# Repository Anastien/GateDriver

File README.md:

# Gate-Drive
This is a 14 Amp OSHW IGBT gate driver circuit, the layout is done using the KiCad EDA suite, more information cab be found on the the detailed documentation.

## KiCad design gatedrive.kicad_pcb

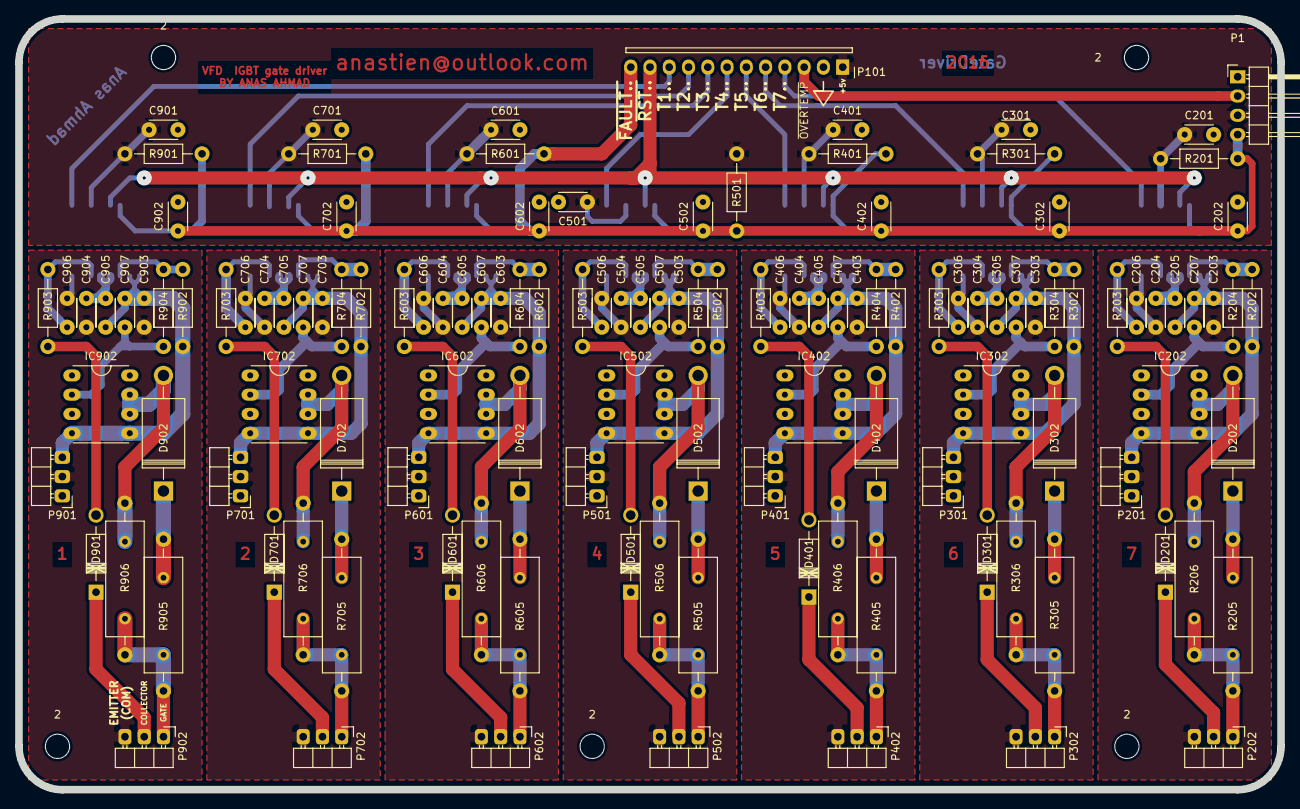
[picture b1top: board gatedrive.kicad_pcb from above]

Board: 2 copper layers, 166.4 x 101.6 mm, 140 parts (0 on the bottom side), 89 nets.

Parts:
2, 2#2, 2#3, 2#4, 2#5: MountingHole_3.2mm_M3
C201, C203, C204, C205, C301, C303, C304, C305, C401, C403, C404, C405, C501, C503, C504, C505, C601, C603, C604, C605, C701, C703, C704, C705, C901, C903, C904, C905: 0.1uF; C_Disc
C202, C302, C402, C502, C602, C702, C902: 330pF; C_Disc
C206, C306, C406, C506, C606, C706, C906: 100pF; C_Disc
C207, C307, C407, C507, C607, C707, C907: 10nF; C_Disc
D201, D301, D401, D501, D601, D701, D901: RGPO2-20; Diode_DO-41_SOD81_Horizontal_RM10
D202, D302, D402, D502, D602, D702, D902: Diode_DO-201AD_Horizontal_RM15
IC201, IC301, IC401, IC501, IC601, IC701, IC901: HCPL-316J; SOIC-16_7.5x10.3mm_Pitch1.27mm
IC202, IC302, IC402, IC502, IC602, IC702, IC902: IXDD614PI; DIP-8_W7.62mm_LongPads
P1: CONN_01X03; Pin_Header_Angled_1x04
P101: Mic General Connector; MICCONN
P201, P202, P301, P302, P401, P402, P501, P502, P601, P602, P701, P702, P901, P902: CONN_01X03; conn
R201, R301, R401, R501, R601, R701, R901: 10K; Resistor_Horizontal_RM10mm
R202, R302, R402, R502, R602, R702, R902: 25K; Resistor_Horizontal_RM10mm
R203, R204, R303, R304, R403, R404, R503, R504, R603, R604, R703, R704, R903, R904: 100; Resistor_Horizontal_RM10mm
R205, R305, R405, R505, R605, R705, R905: 60; Resistor_multi
R206, R306, R406, R506, R606, R706, R906: 30ohm ,0.5W; Resistor_multi

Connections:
15V1: C904.2, C905.1, IC901.12, IC901.13, IC902.1, IC902.3, IC902.8, P901.1
15V2: C704.2, C705.1, IC701.12, IC701.13, IC702.1, IC702.3, IC702.8, P701.1
15V3: C604.2, C605.1, IC601.12, IC601.13, IC602.1, IC602.3, IC602.8, P601.1
15V4: C504.2, C505.1, IC501.12, IC501.13, IC502.1, IC502.3, IC502.8, P501.1
15V5: C404.2, C405.1, IC401.12, IC401.13, IC402.1, IC402.3, IC402.8, P401.1
15V6: C304.2, C305.1, IC301.12, IC301.13, IC302.1, IC302.3, IC302.8, P301.1
15V7: C204.2, C205.1, IC201.12, IC201.13, IC202.1, IC202.3, IC202.8, P201.1
+5V: C201.1, C301.1, C401.1, C501.1, C601.1, C701.1, C901.1, IC201.3, IC301.3, IC401.3, IC501.3, IC601.3, IC701.3, IC901.3, P1.3, P101.1, R201.2, R301.2, R401.2, R501.2, R601.2, R701.2, R901.2
-5v1: C903.1, C905.2, C907.2, IC901.9, IC901.10, IC902.4, IC902.5, P901.3, R902.1
-5v2: C703.1, C705.2, C707.2, IC701.9, IC701.10, IC702.4, IC702.5, P701.3, R702.1
-5v3: C603.1, C605.2, C607.2, IC601.9, IC601.10, IC602.4, IC602.5, P601.3, R602.1
-5v4: C503.1, C505.2, C507.2, IC501.9, IC501.10, IC502.4, IC502.5, P501.3, R502.1
-5v5: C403.1, C405.2, C407.2, IC401.9, IC401.10, IC402.4, IC402.5, P401.3, R402.1
-5v6: C303.1, C305.2, C307.2, IC301.9, IC301.10, IC302.4, IC302.5, P301.3, R302.1
-5v7: C203.1, C205.2, C207.2, IC201.9, IC201.10, IC202.4, IC202.5, P201.3, R202.1
/T1: IC901.1, P101.10
/T2: IC701.1, P101.9
/T3: IC601.1, P101.8
/T4: IC501.1, P101.7
/T5: IC401.1, P101.6
/T6: IC301.1, P101.5
/T7: IC201.1, P101.4
COM1: C903.2, C904.1, C906.2, IC901.16, P901.2, P902.3
COM2: C703.2, C704.1, C706.2, IC701.16, P701.2, P702.3
COM3: C603.2, C604.1, C606.2, IC601.16, P601.2, P602.3
COM4: C503.2, C504.1, C506.2, IC501.16, P501.2, P502.3
COM5: C403.2, C404.1, C406.2, IC401.16, P401.2, P402.3
COM6: C303.2, C304.1, C306.2, IC301.16, P301.2, P302.3
COM7: C203.2, C204.1, C206.2, IC201.16, P201.2, P202.3
G1: P902.1, R905.2, R906.2
G2: P702.1, R705.2, R706.2
G3: P602.1, R605.2, R606.2
G4: P502.1, R505.2, R506.2
G5: P402.1, R405.2, R406.2
G6: P302.1, R305.2, R306.2
G7: P202.1, R205.2, R206.2
GND: C201.2, C202.2, C301.2, C302.2, C401.2, C402.2, C501.2, C502.2, C601.2, C602.2, C701.2, C702.2, C901.2, C902.2, IC201.2, IC201.4, IC201.8, IC301.2, IC301.4, IC301.8, IC401.2, IC401.4, IC401.8, IC501.2, IC501.4, IC501.8, IC601.2, IC601.4, IC601.8, IC701.2, IC701.4, IC701.8, IC901.2, IC901.4, IC901.8, P1.1, P101.2
unnamed: C206.1, IC201.14, R203.1
unnamed: C207.1, IC202.2, R204.1
unnamed: C306.1, IC301.14, R303.1
unnamed: C307.1, IC302.2, R304.1
unnamed: C406.1, IC401.14, R403.1
unnamed: C407.1, IC402.2, R404.1
unnamed: C506.1, IC501.14, R503.1
unnamed: C507.1, IC502.2, R504.1
unnamed: C606.1, IC601.14, R603.1
unnamed: C607.1, IC602.2, R604.1
unnamed: C706.1, IC701.14, R703.1
unnamed: C707.1, IC702.2, R704.1
unnamed: C906.1, IC901.14, R903.1
unnamed: C907.1, IC902.2, R904.1
unnamed: D201.2, R203.2
unnamed: D202.1, R205.1
unnamed: D202.2, IC202.6, IC202.7, R206.1
unnamed: D301.2, R303.2
unnamed: D302.1, R305.1
unnamed: D302.2, IC302.6, IC302.7, R306.1
unnamed: D401.2, R403.2
unnamed: D402.1, R405.1
unnamed: D402.2, IC402.6, IC402.7, R406.1
unnamed: D501.2, R503.2
unnamed: D502.1, R505.1
unnamed: D502.2, IC502.6, IC502.7, R506.1
unnamed: D601.2, R603.2
unnamed: D602.1, R605.1
unnamed: D602.2, IC602.6, IC602.7, R606.1
unnamed: D701.2, R703.2
unnamed: D702.1, R705.1
unnamed: D702.2, IC702.6, IC702.7, R706.1
unnamed: D901.2, R903.2
unnamed: D902.1, R905.1
unnamed: D902.2, IC902.6, IC902.7, R906.1
unnamed: IC201.11, R202.2, R204.2
unnamed: IC301.11, R302.2, R304.2
unnamed: IC401.11, R402.2, R404.2
unnamed: IC501.11, R502.2, R504.2
unnamed: IC601.11, R602.2, R604.2
unnamed: IC701.11, R702.2, R704.2
unnamed: IC901.11, R902.2, R904.2
c1: D901.1, P902.2
c2: D701.1, P702.2
c3: D601.1, P602.2
c4: D501.1, P502.2
c5: D401.1, P402.2
c6: D301.1, P302.2
c7: D201.1, P202.2
~FAULT: C202.1, C302.1, C402.1, C502.1, C602.1, C702.1, C902.1, IC201.6, IC301.6, IC401.6, IC501.6, IC601.6, IC701.6, IC901.6, P1.4, P101.12, R201.1, R301.1, R401.1, R501.1, R601.1, R701.1, R901.1
~OVERTEMP: P1.2, P101.3
~RST: IC201.5, IC301.5, IC401.5, IC501.5, IC601.5, IC701.5, IC901.5, P101.11

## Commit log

2016-03-03 start
2016-03-04 Prototype
2016-03-04 sending to m.n
2016-03-08 updsting hcpl-316j ic footprint and layout
2016-04-08 cleaning the repo
2016-04-11 uding HCPL-361J modified symbol
2016-04-11 Create gh-pages branch via GitHub
2016-04-11 git page
2016-04-11 add read me
2016-04-11 cleaning
2016-04-12 cleaning the schematic
2016-04-22 completion of the layout, initial layout of the protection circuit, reducing number of circuit to 7
2016-06-08 yet another enhancements .
    the protection section still is incomplete.
2016-06-24 packup
2016-07-05 parting the protection from the GD
